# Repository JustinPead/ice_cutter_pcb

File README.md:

# ice_cutter_pcb
The PCB for the ice cutter project

This is a component for the greater project of an automated Ice cutting rig

The PCB is responsible for providing the power, receiving the power setting (potentiometer) and providing information on the current status (7 Seg and LEDS)
It has an onboard temperature sensor to determine the initial conditions for the ice rig.

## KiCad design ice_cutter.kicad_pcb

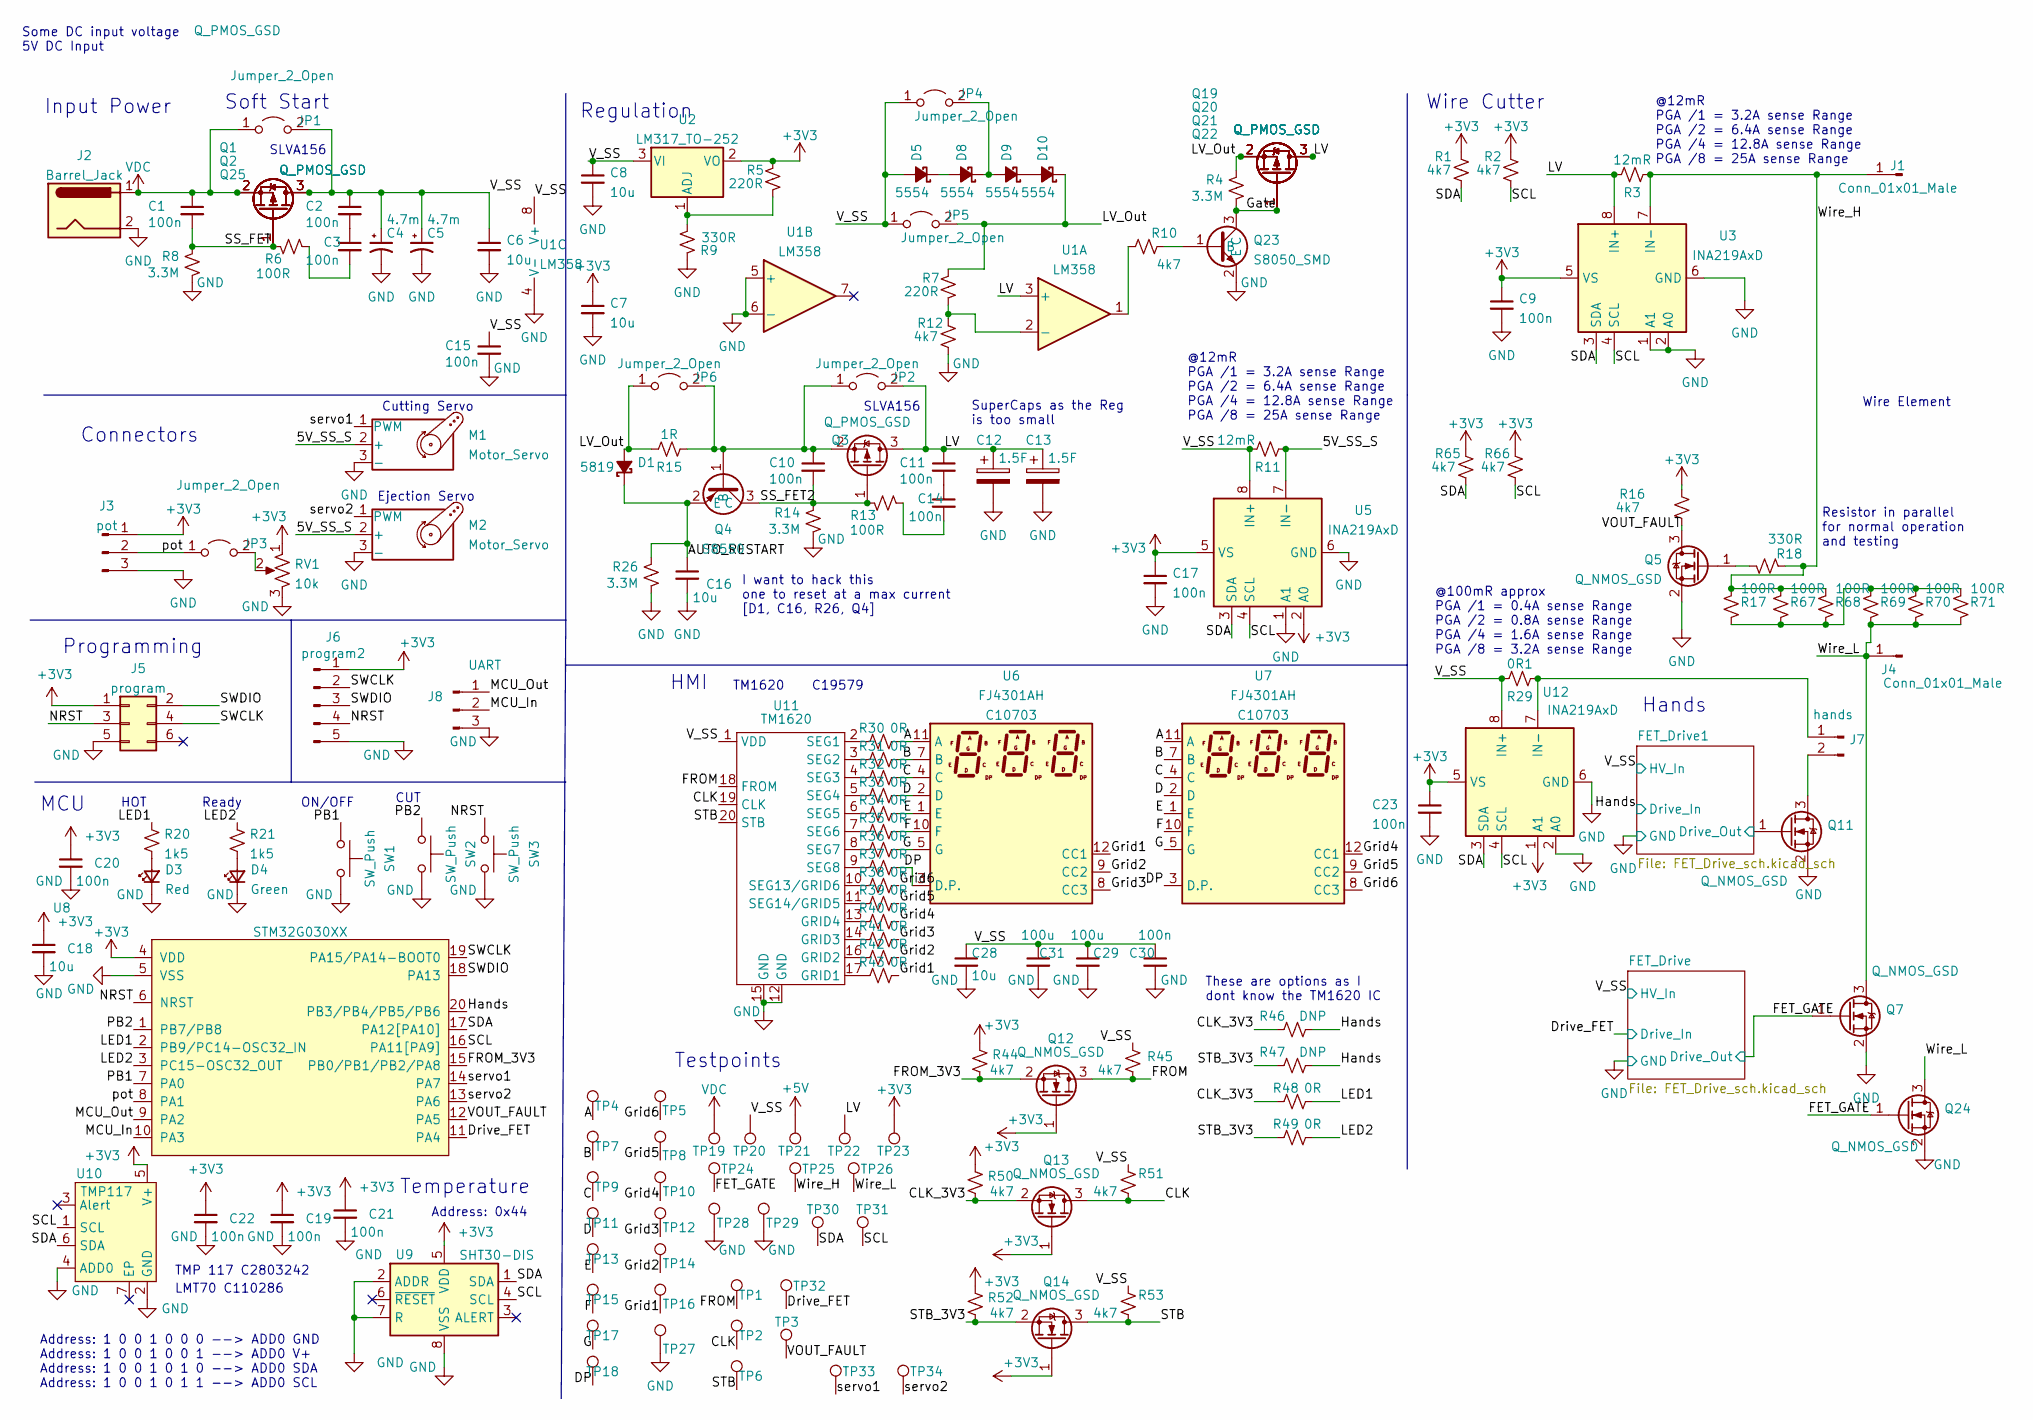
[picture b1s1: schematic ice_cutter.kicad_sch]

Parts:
C1, C2, C3, C9, C10, C11, C14, C15, C17, C19, C20, C21, C22, C23, C29: 100n; C_0402_1005Metric; LCSC C307331
C4, C5: 4.7m; CP_Radial_D14.0mm_P5.00mm
C6, C7, C8, C16, C18, C28: 10u; C_0603_1608Metric; LCSC C96446
C12, C13: 1.5F; SP-5R5-Z155VY; LCSC C128277
C30, C31: 100u; C_1206_3216Metric_Pad1.33x1.80mm_HandSolder; LCSC C15008
D1: 5819; D_SOD-123; LCSC C963381
D3: Red; D_0603_1608Metric; LCSC C2286
D4: Green; D_0603_1608Metric; LCSC C72043
D5, D8, D9, D10: 5554; D_SMA; LCSC C22452
J1, J4: Conn_01x01_Male; SMD_Pad_15x10
J2: Barrel_Jack; Barrel_Jack_2A_C84007; LCSC C84007
J3: pot; PinHeader_1x03_P2.54mm_Vertical
J5: program; TC2030NL
J6: program2; PinHeader_1x05_P2.54mm_Vertical
J7: hands; PinHeader_1x02_P2.54mm_Vertical
J8: UART; PinHeader_1x03_P2.54mm_Vertical
JP1, JP2, JP3, JP4, JP5, JP6: Jumper_2_Open; SolderJumper-2_P1.3mm_Open_RoundedPad1.0x1.5mm
M1, M2: Motor_Servo; PinHeader_1x03_P2.54mm_Vertical
Q1, Q2, Q3, Q19, Q20, Q21, Q22, Q25: Q_PMOS_GSD; SOT-23; LCSC C15127
Q4: S8550; SOT-23; LCSC C8542
Q5, Q12, Q13, Q14: Q_NMOS_GSD; SOT-23; LCSC C20917
Q7, Q11, Q24: Q_NMOS_GSD; TO-252-2; LCSC C709962
Q23: S8050_SMD; SOT-23; LCSC C2150
R1, R2, R10, R12, R16, R44, R45, R50, R51, R52, R53, R65, R66: 4k7; R_0402_1005Metric; LCSC C25900
R3, R11: 12mR; R_2512_6332Metric; LCSC C323773
R4, R8, R14, R26: 3.3M; R_0402_1005Metric; LCSC C25741
R5, R7: 220R; R_0402_1005Metric; LCSC C25091
R6, R13: 100R; R_0402_1005Metric; LCSC C25076
R9, R18: 330R; R_0402_1005Metric; LCSC C25104
R15: 1R; R_2512_6332Metric; LCSC C11254
R17, R67, R68, R69, R70, R71: 100R; R_1206_3216Metric; LCSC C17901
R20, R21: 1k5; R_0402_1005Metric; LCSC C25867
R29: 0R1; R_1206_3216Metric; LCSC C25334
R30, R31, R32, R33, R34, R35, R36, R37, R38, R39, R40, R41, R42, R43, R48, R49: 0R; R_0402_1005Metric; LCSC C17168
R46, R47: DNP; R_0402_1005Metric; LCSC C17168
RV1: 10k; RK09_THT_Pot_C209770; LCSC C209770
SW1, SW2, SW3: SW_Push; SW_SPST_TL3342; LCSC C318884
TP1, TP2, TP3, TP4, TP5, TP6, TP7, TP8, TP9, TP10, TP11, TP12, TP13, TP14, TP15, TP16, TP17, TP18, TP19, TP20, TP21, TP22, TP23, TP24, TP25, TP26, TP27, TP28, TP29, TP30, TP31, TP32, TP33, TP34: TestPoint; TestPoint_Pad_D2.0mm
U1: LM358; SOIC-8_3.9x4.9mm_P1.27mm
U2: LM317_TO-252; TO-252-2; LCSC C75510
U3, U5, U12: INA219AxD; SOIC-8_3.9x4.9mm_P1.27mm; LCSC C138706
U6, U7: FJ4301AH; 7_Seg_x3; LCSC C10703
U8: STM32G030XX; TSSOP-20_4.4x6.5mm_P0.65mm; LCSC C529330
U9: SHT30-DIS; Sensirion_DFN-8-1EP_2.5x2.5mm_P0.5mm_EP1.1x1.7mm; LCSC C77361
U10: TMP117; WSON-6-1EP_2x2mm_P0.65mm_EP1x1.6mm; LCSC C2803242
U11: TM1620; SOP-20_7.5x12.8mm_P1.27mm; LCSC C19579

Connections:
+3V3: C7.1, C9.1, C17.1, C18.1, C19.1, C20.1, C21.1, C22.1, C23.1, J3.1, J5.1, J6.1, Q12.1 (G), Q13.1 (G), Q14.1 (G), R1.2, R2.2, R5.2, R16.2, R44.1, R50.1, R52.1, R65.2, R66.2, RV1.1, TP23.1, U2.2 (VO), U3.5 (VS), U5.2 (A0), U5.5 (VS), U8.4 (VDD), U9.5 (VDD), U10.5 (V+), U12.1 (A1), U12.5 (VS)
+5V: TP21.1
/5V_SS_S: M1.2 (+), M2.2 (+), R11.2, U5.7 (IN-)
/A: R30.2, TP4.1, U6.11 (A), U7.11 (A)
/AUTO_RESTART: C16.1, D1.1 (K), Q4.2 (E), R26.1
/B: R31.2, TP7.1, U6.7 (B), U7.7 (B)
/C: R32.2, TP9.1, U6.4 (C), U7.4 (C)
/CLK: Q13.3 (D), R51.1, TP2.1, U11.19 (CLK)
/CLK_3V3: Q13.2 (S), R46.1, R48.1, R50.2
/D: R33.2, TP11.1, U6.2 (D), U7.2 (D)
/DP: R37.2, TP18.1, U6.3 (D.P.), U7.3 (D.P.)
/Drive_FET: TP32.1, U8.11 (PA4); also elsewhere on the board
/E: R34.2, TP13.1, U6.1 (E), U7.1 (E)
/F: R35.2, TP15.1, U6.10 (F), U7.10 (F)
/FET_Drive1/Drive_Out: Q11.1 (G); also elsewhere on the board
/FET_GATE: Q7.1 (G), Q24.1 (G), TP24.1; also elsewhere on the board
/FROM: Q12.3 (D), R45.1, TP1.1, U11.18 (FROM)
/FROM_3V3: Q12.2 (S), R44.2, U8.15 (PB0/PB1/PB2/PA8)
/G: R36.2, TP17.1, U6.5 (G), U7.5 (G)
/Gate: Q19.1 (G), Q20.1 (G), Q21.1 (G), Q22.1 (G), Q23.3 (C), R4.2
/Grid1: R43.2, TP16.1, U6.12 (CC1)
/Grid2: R42.2, TP14.1, U6.9 (CC2)
/Grid3: R41.2, TP12.1, U6.8 (CC3)
/Grid4: R40.2, TP10.1, U7.12 (CC1)
/Grid5: R39.2, TP8.1, U7.9 (CC2)
/Grid6: R38.2, TP5.1, U7.8 (CC3)
/Hands: R46.2, R47.2, U8.20 (PB3/PB4/PB5/PB6); also elsewhere on the board
/LED1: R20.1, R48.2, U8.2 (PB9/PC14-OSC32_IN)
/LED2: R21.1, R49.2, U8.3 (PC15-OSC32_OUT)
/LV: C11.1, C12.1, C13.1, JP2.2 (B), Q3.3 (D), Q19.3 (D), Q20.3 (D), Q21.3 (D), Q22.3 (D), R3.1, TP22.1, U1.3 (+), U3.8 (IN+)
/LV_Out: D1.2 (A), D10.1 (K), JP5.2 (B), JP6.1 (A), Q19.2 (S), Q20.2 (S), Q21.2 (S), Q22.2 (S), R4.1, R7.2, R15.1
/MCU_In: J8.2, U8.10 (PA3)
/MCU_Out: J8.1, U8.9 (PA2)
/NRST: J5.3, J6.4, SW3.1, U8.6 (NRST)
/PB1: SW1.1, U8.7 (PA0)
/PB2: SW2.1, U8.1 (PB7/PB8)
/SCL: R2.1, R66.1, TP31.1, U3.4 (SCL), U5.4 (SCL), U8.16 (PA11[PA9]), U9.4 (SCL), U10.1 (SCL), U12.4 (SCL)
/SDA: R1.1, R65.1, TP30.1, U3.3 (SDA), U5.3 (SDA), U8.17 (PA12[PA10]), U9.1 (SDA), U10.6 (SDA), U12.3 (SDA)
/SS_FET: C1.2, Q1.1 (G), Q2.1 (G), Q25.1 (G), R6.1, R8.1
/SS_FET2: C10.2, Q3.1 (G), Q4.3 (C), R13.1, R14.1
/STB: Q14.3 (D), R53.1, TP6.1, U11.20 (STB)
/STB_3V3: Q14.2 (S), R47.1, R49.1, R52.2
/SWCLK: J5.4, J6.2, U8.19 (PA15/PA14-BOOT0)
/SWDIO: J5.2, J6.3, U8.18 (PA13)
/VOUT_FAULT: Q5.3 (D), R16.1, TP3.1, U8.12 (PA5)
/V_SS: C2.1, C4.1, C5.1, C6.1, C8.1, C15.1, C28.1, C29.1, C30.1, C31.1, D5.2 (A), JP1.2 (B), JP4.1 (A), JP5.1 (A), Q1.3 (D), Q2.3 (D), Q25.3 (D), R11.1, R29.1, R45.2, R51.2, R53.2, TP20.1, U1.8 (V+), U2.3 (VI), U5.8 (IN+), U11.1 (VDD), U12.8 (IN+); also elsewhere on the board
/Wire_H: J1.1, R3.2, R17.1, R18.1, R67.1, R68.1, TP25.1, U3.7 (IN-)
/Wire_L: J4.1, Q7.3 (D), Q24.3 (D), R69.2, R70.2, R71.2, TP26.1
/pot: J3.2, JP3.1 (A), U8.8 (PA1)
/servo1: M1.1 (PWM), TP33.1, U8.14 (PA7)
/servo2: M2.1 (PWM), TP34.1, U8.13 (PA6)
GND: C4.2, C5.2, C6.2, C7.2, C8.2, C9.2, C12.2, C13.2, C15.2, C16.2, C17.2, C18.2, C19.2, C20.2, C21.2, C22.2, C23.2, C28.2, C29.2, C30.2, C31.2, D3.1 (K), D4.1 (K), J2.2, J3.3, J5.5, J6.5, J8.3, M1.3 (-), M2.3 (-), Q5.2 (S), Q7.2 (S), Q11.2 (S), Q23.2 (E), Q24.2 (S), R8.2, R9.1, R12.1, R14.2, R26.2, RV1.3, SW1.2, SW2.2, SW3.2, TP27.1, TP28.1, TP29.1, U1.4 (V-), U1.5 (+), U1.6 (-), U3.1 (A1), U3.2 (A0), U3.6 (GND), U5.1 (A1), U5.6 (GND), U8.5 (VSS), U9.2 (ADDR), U9.7 (R), U9.8 (VSS), U9.9 (VSS), U10.2 (GND), U10.4 (ADD0), U11.12 (GND), U11.15 (GND), U12.2 (A0), U12.6 (GND); also elsewhere on the board
unnamed: C2.2, C3.1
unnamed: C3.2, R6.2
unnamed: C10.1, JP2.1 (A), JP6.2 (B), Q3.2 (S), Q4.1 (B), R15.2
unnamed: C11.2, C14.1
unnamed: C14.2, R13.2
unnamed: D3.2 (A), R20.2
unnamed: D4.2 (A), R21.2
unnamed: D5.1 (K), D8.2 (A)
unnamed: D8.1 (K), D9.2 (A), JP4.2 (B)
unnamed: D9.1 (K), D10.2 (A)
unnamed: J7.1, R29.2, U12.7 (IN-)
unnamed: J7.2, Q11.3 (D)
unnamed: JP3.2 (B), RV1.2
unnamed: Q5.1 (G), R18.2
unnamed: Q23.1 (B), R10.1
unnamed: R5.1, R9.2, U2.1 (ADJ)
unnamed: R10.2, U1.1
unnamed: R7.1, R12.2, U1.2 (-)
unnamed: R30.1, U11.2 (SEG1)
unnamed: R31.1, U11.3 (SEG2)
unnamed: R32.1, U11.4 (SEG3)
unnamed: R33.1, U11.5 (SEG4)
unnamed: R34.1, U11.6 (SEG5)
unnamed: R35.1, U11.7 (SEG6)
unnamed: R36.1, U11.8 (SEG7)
unnamed: R37.1, U11.9 (SEG8)
unnamed: R38.1, U11.10 (SEG13/GRID6)
unnamed: R39.1, U11.11 (SEG14/GRID5)
unnamed: R40.1, U11.13 (GRID4)
unnamed: R41.1, U11.14 (GRID3)
unnamed: R42.1, U11.16 (GRID2)
unnamed: R43.1, U11.17 (GRID1)
unnamed: R17.2, R67.2, R68.2, R69.1, R70.1, R71.1
VDC: C1.1, J2.1, JP1.1 (A), Q1.2 (S), Q2.2 (S), Q25.2 (S), TP19.1

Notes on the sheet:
ON/OFF
Ejection Servo
Programming
Regulation
TM1620 C19579
SLVA156
Connectors
Resistor in parallel for normal operation and testing
CUT
Address: 0x44
LMT70 C110286
HMI
TMP 117 C2803242
Ready
Some DC input voltage 5V DC Input
These are options as I dont know the TM1620 IC
I want to hack this one to reset at a max current [D1, C16, R26, Q4]
Hands
MCU
SuperCaps as the Reg is too small
@12mR PGA /1 = 3.2A sense Range PGA /2 = 6.4A sense Range PGA /4 = 12.8A sense Range PGA /8 = 25A sense Range
Input Power
Soft Start
HOT
Cutting Servo
Temperature
Address: 1 0 0 1 0 0 0 --> ADD0 GND Address: 1 0 0 1 0 0 1 --> ADD0 V+ Address: 1 0 0 1 0 1 0 --> ADD0 SDA Address: 1 0 0 1 0 1 1 --> ADD0 SCL
Wire Element
Testpoints
Wire Cutter
@100mR approx PGA /1 = 0.4A sense Range PGA /2 = 0.8A sense Range PGA /4 = 1.6A sense Range PGA /8 = 3.2A sense Range

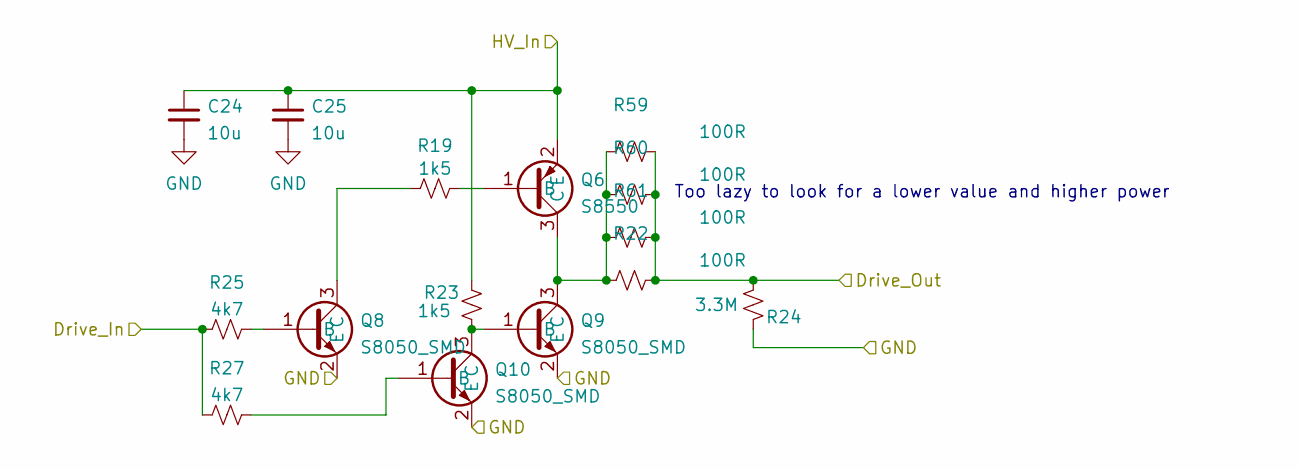
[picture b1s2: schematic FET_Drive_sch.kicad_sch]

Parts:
C24, C25: 10u; C_0603_1608Metric; LCSC C96446
Q6: S8550; SOT-23; LCSC C8542
Q8, Q9, Q10: S8050_SMD; SOT-23; LCSC C2150
R19, R23: 1k5; R_0402_1005Metric; LCSC C25867
R22, R59, R60, R61: 100R; R_0402_1005Metric; LCSC C25076
R24: 3.3M; R_0402_1005Metric; LCSC C25741
R25, R27: 4k7; R_0402_1005Metric; LCSC C25900

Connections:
/Drive_FET: R25.1, R27.1; also elsewhere on the board
/FET_GATE: R22.2, R24.1, R59.2, R60.2, R61.2; also elsewhere on the board
/V_SS: C24.1, C25.1, Q6.2 (E), R23.2; also elsewhere on the board
GND: C24.2, C25.2, Q8.2 (E), Q9.2 (E), Q10.2 (E), R24.2; also elsewhere on the board
unnamed: Q6.1 (B), R19.2
unnamed: Q6.3 (C), Q9.3 (C), R22.1, R59.1, R60.1, R61.1
unnamed: Q8.1 (B), R25.2
unnamed: Q8.3 (C), R19.1
unnamed: Q10.1 (B), R27.2
unnamed: Q9.1 (B), Q10.3 (C), R23.1

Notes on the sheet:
Too lazy to look for a lower value and higher power

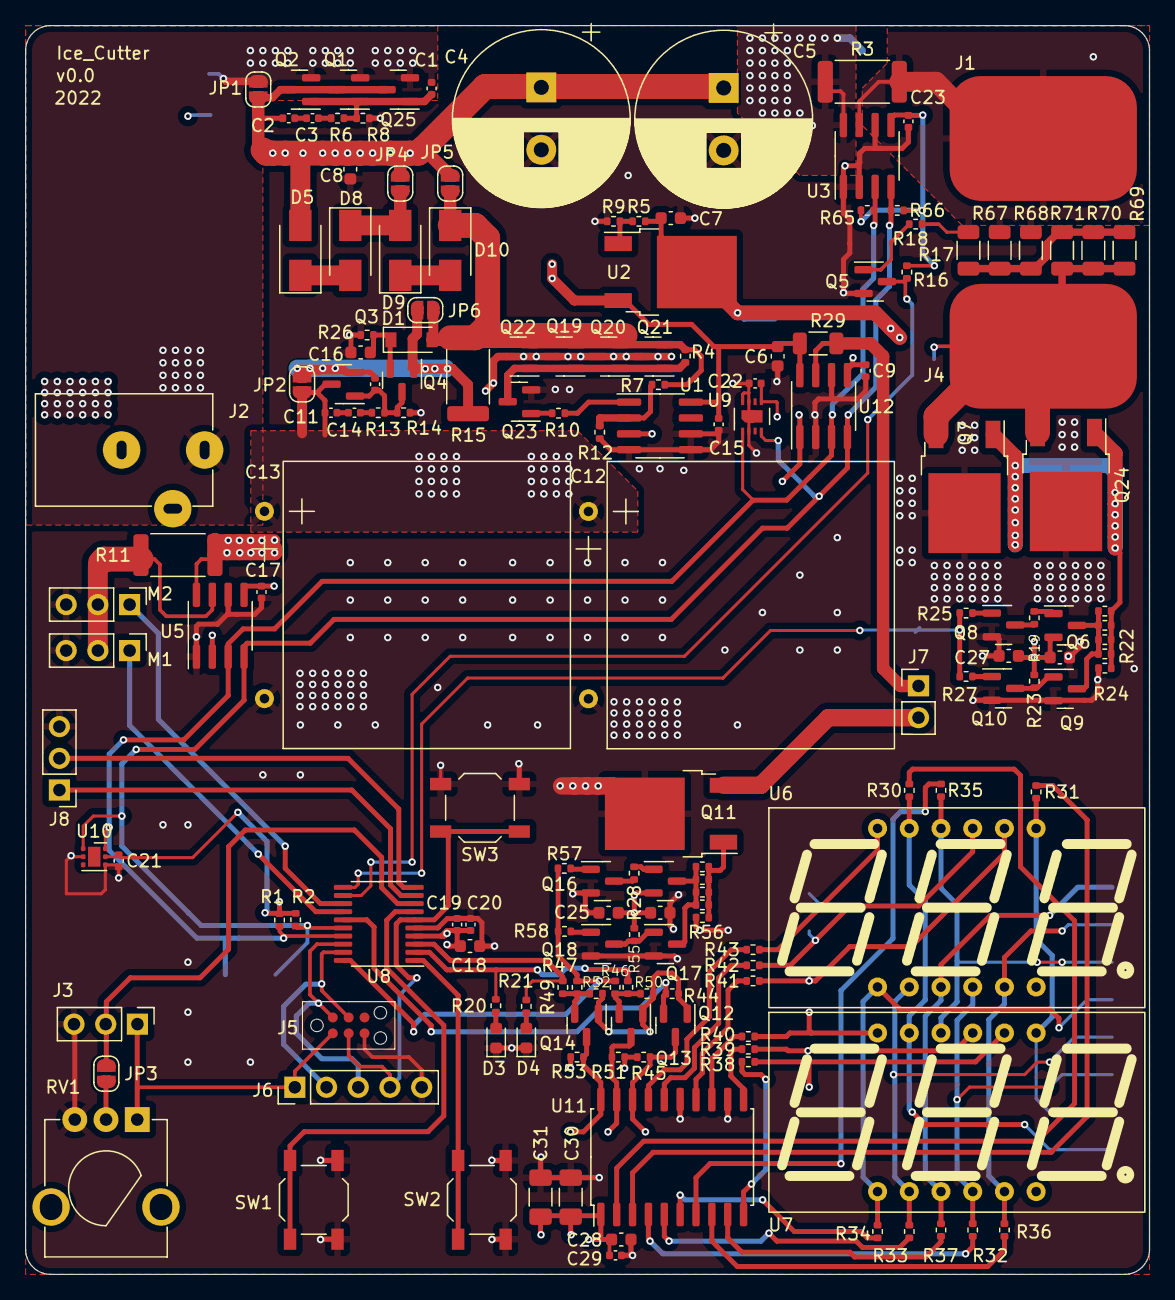
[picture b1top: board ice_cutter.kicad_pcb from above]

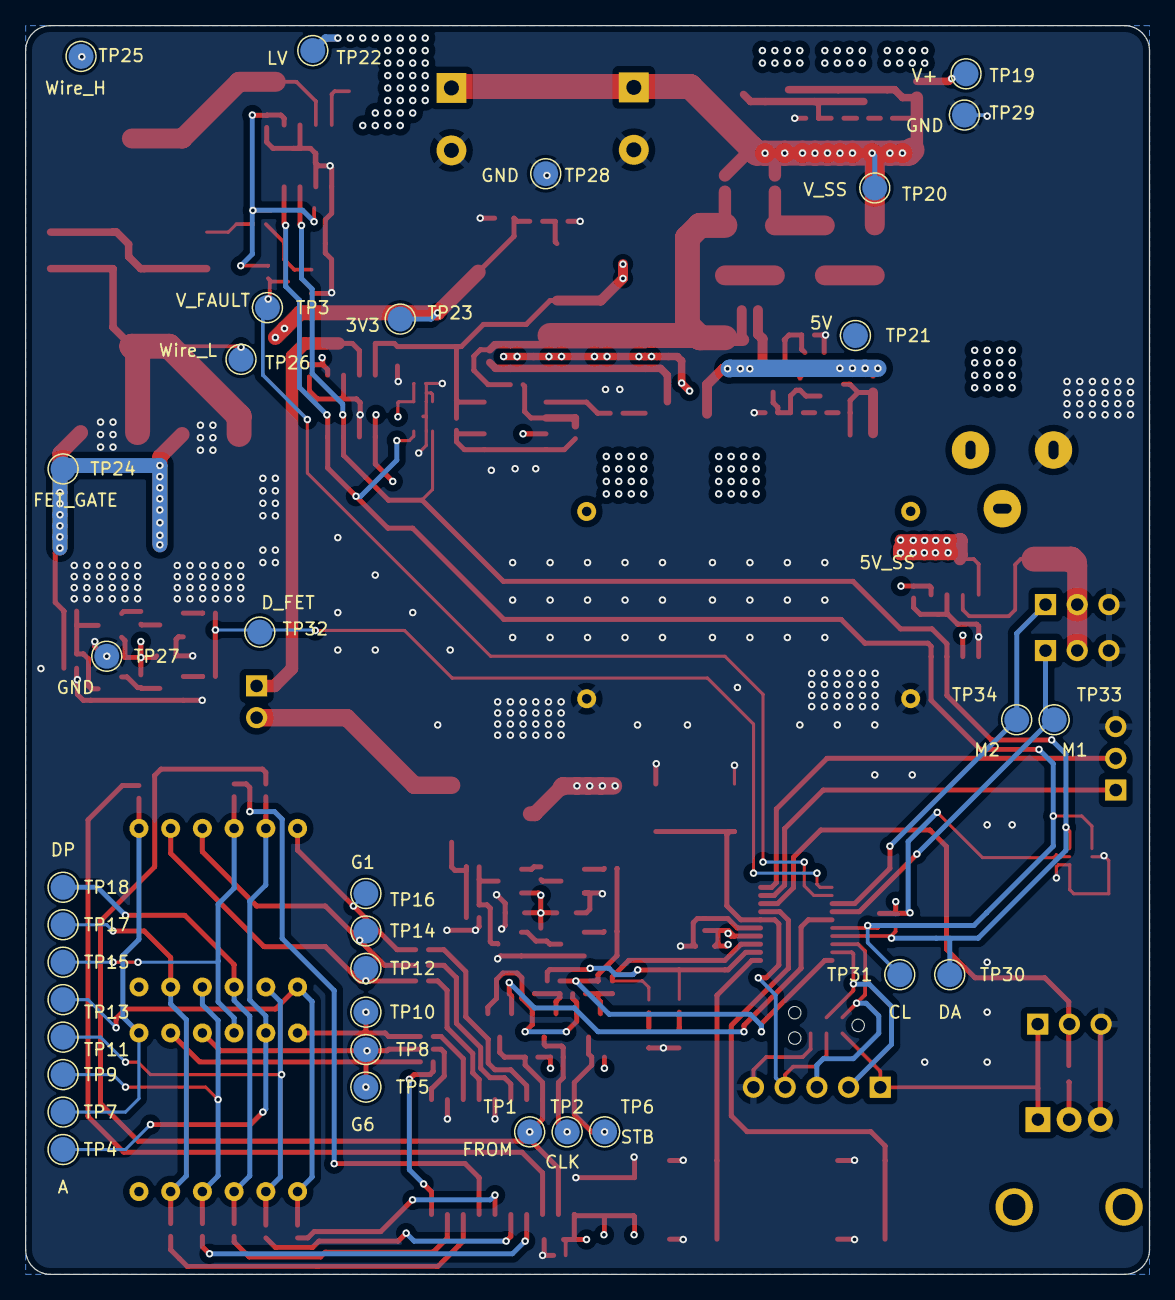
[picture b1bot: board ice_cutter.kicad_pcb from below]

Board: 4 copper layers, 90.0 x 100.0 mm, 199 parts (34 on the bottom side), 97 nets.

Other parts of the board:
C26, C27: 10u; C_0603_1608Metric
Q15: S8550; SOT-23
Q16, Q17, Q18: S8050_SMD; SOT-23
R28, R55: 1k5; R_0402_1005Metric
R54, R62, R63, R64: 100R; R_0402_1005Metric
R56: 3.3M; R_0402_1005Metric
R57, R58: 4k7; R_0402_1005Metric

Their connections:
/FET_Drive1/Drive_Out: R54.2, R56.1, R62.2, R63.2, R64.2; also elsewhere on the board
/Hands: R57.1, R58.1; also elsewhere on the board
/V_SS: C26.1, C27.1, Q15.2 (E), R55.2; also elsewhere on the board
GND: C26.2, C27.2, Q16.2 (E), Q17.2 (E), Q18.2 (E), R56.2; also elsewhere on the board
unnamed: Q15.1 (B), R28.2
unnamed: Q15.3 (C), Q17.3 (C), R54.1, R62.1, R63.1, R64.1
unnamed: Q16.1 (B), R57.2
unnamed: Q16.3 (C), R28.1
unnamed: Q17.1 (B), Q18.3 (C), R55.1
unnamed: Q18.1 (B), R58.2

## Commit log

2022-05-24 tracking datasheets, and schematic improvements
2022-05-24 inclusion of motors and schematic improvements
2022-05-30 Added TM1620 symbol to library(LED drive control)
2022-06-08 Changes in schematic, added Soft starts everywhere...
2022-06-08 added barrel jack and super caps
2022-06-09 added some TP and some 0R resistors and a program header for simple programming
2022-06-09 added more TP
2022-06-10 Think I have finished the schematic
2022-06-10 Some layout done, no wiring yet
2022-06-11 moree wiring done, shrank board slightly. Unsure whether 4 layer is necessary
2022-06-11 more wiring done, shrank board slightly. Unsure whether 4 layer is necessary - HADNT saved PCB
2022-06-11 got lazy, went 4 layer. Some of layer 3 done. progressing. Mainly committing for board chronological how to sake. Added Caps on the TM1620
2022-06-11 more PCB progress
2022-06-11 finished v0 I hope
2022-06-11 additional save
2022-06-12 improved schematic and changed the shunt resistors
2022-06-12 Neatened the schematic
2022-06-14 modified the system to operate on 5V - bypassed all regs and changed the BIG FET to a lower threshold V
2022-06-14 major schematic changes, 5V is now the highest voltage, added more FETs for Wire conduction, more for SS, opamp for current hack, removed Regs, XT60 and significantly changed wiring and R values for 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
2022-06-15 more mods, taking it to a solution. Mostly on layer 3 and power management
2022-06-15 potential new version. Still to do Silkscreen and resistor value confirmations
2022-06-15 hadnt saved... this is the last commit message
2022-06-15 5V version - I hope it works
2022-06-15 havent saved again...
